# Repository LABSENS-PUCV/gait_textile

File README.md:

# gait_textile
"Detection of Human Gait Phases Using Textile Pressure Sensors: A Low Cost and Pervasive Approach" paper public repository. Created by Milovic, M.; Pizarro, F.; Fingerhuth, S.; Hermosilla, G.; Farías, G.; Yunge, D..

Based on the previous paper "Easy-to-build textile pressure sensor" published in Sensors. Created by Pizarro, F.; Villavicencio, P.; Yunge, D.; Rodríguez, M.; Hermosilla, G.; Leiva, A.

The structure of the repository is as follows:

1.- "Acquisition_board" directory contains all the files associated to the elaboration of the acquisition board used in the pants, considering PCB, code of the microcontroller, and 3D object files of the case used for the acquisition board.

2.- "Features_Classification" directory contains only one Jupyter Notebook file that contains the processes implemented to extract features from the data of the sensors, but also to elaborate the classification models and testing them.

3.- "Annotation_code" directory contains a file called "GaitAnnotation", which was written in Python and contains the method for labeling gait phases with a WebCam. This file requires a lot of libraries and BlazePose model to avhieve good 
results when assessing the position of different parts of the body.

4.- "Preprocessing" directory, which has all the Matlab code for preprocessing the data.

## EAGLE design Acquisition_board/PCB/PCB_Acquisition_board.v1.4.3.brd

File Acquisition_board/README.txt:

1.- "Case" directory contains 2 STL files that are the 3D objects printed to make the case of the acquisition board.

2.- "Code" directory contains the Arduino code loaded into an STM32 "Blue pill" development board which is part of the acquisition board.

3.- "PCB" directory includes 2 files, one of them is the layout of the PCB and the other one is the schematic diagram, both were made in Eagle.

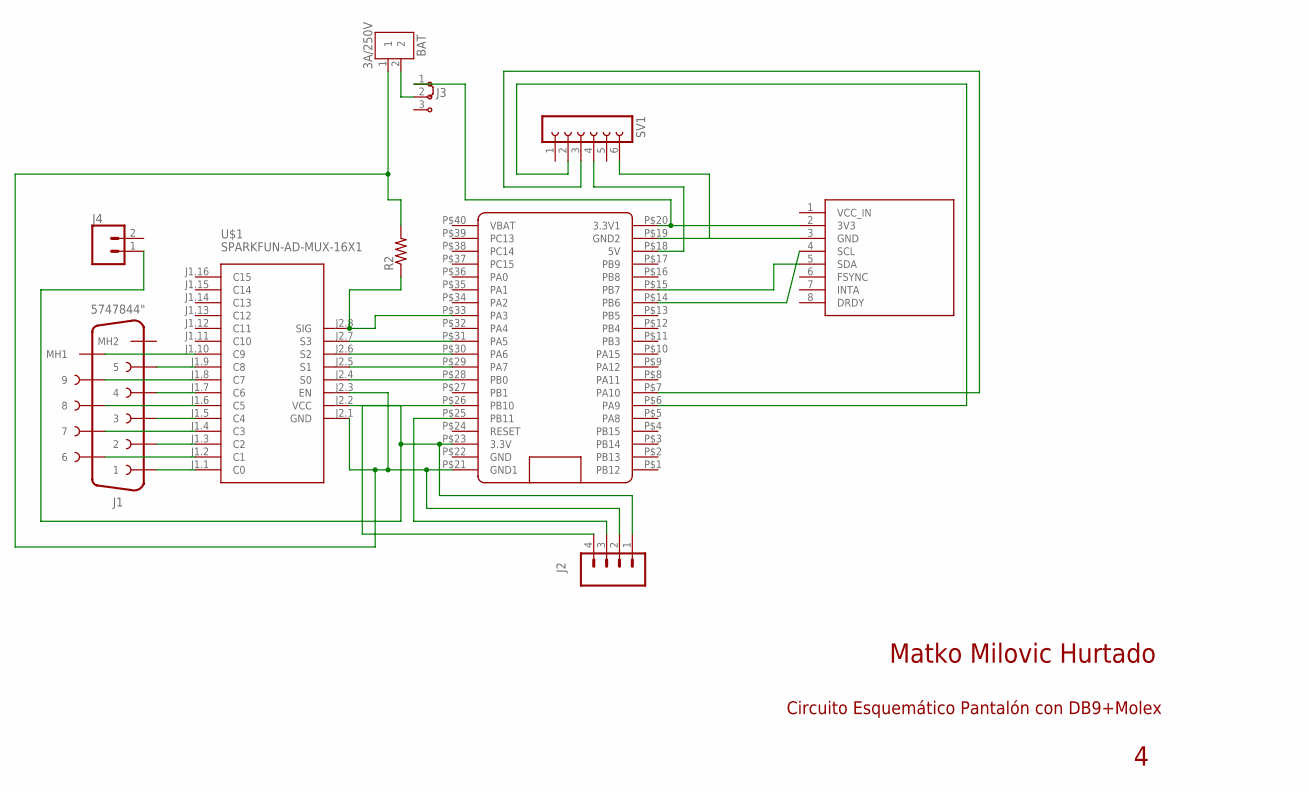
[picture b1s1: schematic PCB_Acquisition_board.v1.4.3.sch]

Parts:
BAT: 3A/250V; B2B-XH-A
J1: 5747844"; 5747844-4
J2: CONN_04; 1X04
J3: J2X2MM; 04C
J4: CONN_02; 1X02
R2: R-US_0309/10; 0309/10
SV1: FE06-1; FE06
U$1: SPARKFUN-AD-MUX-16X1
U$2: GY-86
U$5: BLUE_PILL

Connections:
MH1: J1.MH2 (MH1), U$1.J1.10 (C9)
unnamed: BAT.2, J3.2
unnamed: U$2.4 (SCL), U$5.P$14 (PB6)
unnamed: J1.1, U$1.J1.1 (C0)
unnamed: J1.6, U$1.J1.2 (C1)
unnamed: J1.2, U$1.J1.3 (C2)
unnamed: J1.7, U$1.J1.4 (C3)
unnamed: J1.3, U$1.J1.5 (C4)
unnamed: J1.8, U$1.J1.6 (C5)
unnamed: J1.4, U$1.J1.7 (C6)
unnamed: J1.9, U$1.J1.8 (C7)
unnamed: J2.3, U$5.P$25 (PB11)
unnamed: U$1.J2.4 (S0), U$5.P$28 (PB0)
unnamed: J1.5, U$1.J1.9 (C8)
unnamed: J2.1, J4.1, U$1.J2.2 (VCC), U$5.P$23 (3.3V)
unnamed: BAT.1, J2.2, R2.2, U$1.J2.1 (GND), U$1.J2.3 (EN), U$5.P$21 (GND1)
unnamed: J2.4, U$5.P$26 (PB10)
unnamed: U$2.5 (SDA), U$5.P$15 (PB7)
unnamed: SV1.3, U$5.P$7 (PA10)
unnamed: SV1.2, U$5.P$6 (PA9)
unnamed: U$1.J2.5 (S1), U$5.P$29 (PA7)
unnamed: U$1.J2.6 (S2), U$5.P$30 (PA6)
unnamed: U$1.J2.7 (S3), U$5.P$31 (PA5)
unnamed: R2.1, U$1.J2.8 (SIG), U$5.P$33 (PA3)
unnamed: SV1.6, U$2.3 (GND), U$5.P$19 (GND2)
unnamed: J3.1, U$2.2 (3V3), U$5.P$20 (3.3V1)
unnamed: SV1.4, U$5.P$18 (5V)

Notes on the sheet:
Circuito Esquemático Pantalón con DB9+Molex
Matko Milovic Hurtado

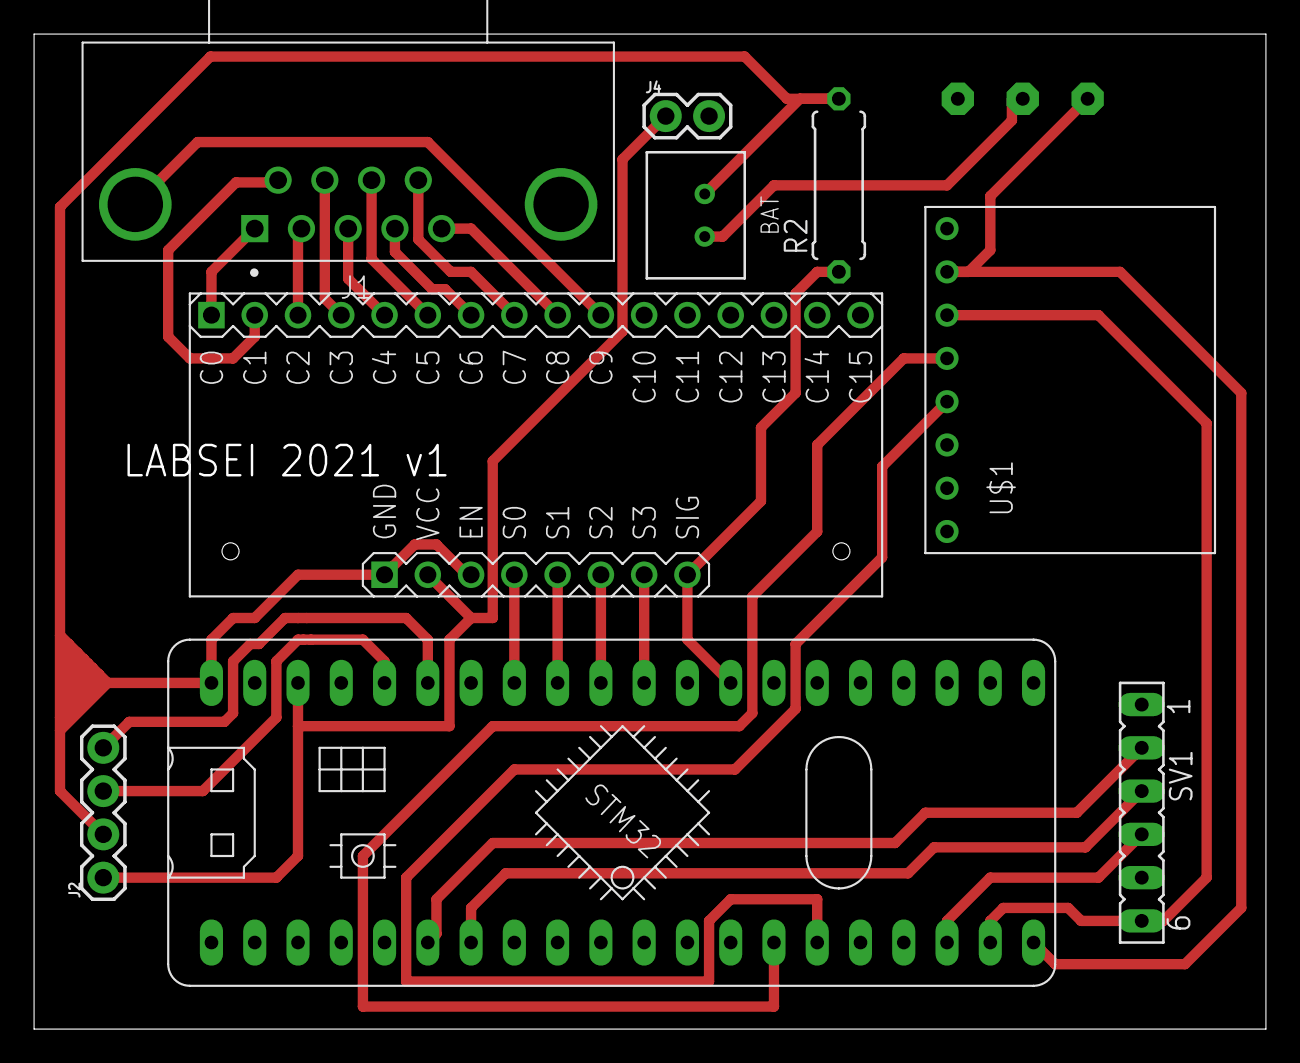
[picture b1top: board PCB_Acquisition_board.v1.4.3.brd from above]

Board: 2 copper layers, 72.3 x 58.4 mm, 10 parts (1 on the bottom side), 27 nets.

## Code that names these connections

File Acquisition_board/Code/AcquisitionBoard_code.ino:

#include "MPU9250.h"
#include <Adafruit_BMP280.h>
#include <Wire.h>

Adafruit_BMP280 bmp; // I2C
MPU9250 IMU(Wire,0x68);
int status;
float alturaB, alturaDIF;
const int num_sensores=10;
double Rref= 2200.00;                  //Resistencia del divisor de tension
unsigned long tiempus;          // Variable para almacena el tiempo de ejecucion
int S0 = PB0;
int S1 = PA7;
int S2 = PA6;
int S3 = PA5;
int muxADC = PA3;
double textiles[num_sensores] = {0.00};
double val;
double res;                        //Resistencia del sensor
double vout;                       //Voltaje del ADC
String buff = "";                  // Buffer trama

// Muestreo
volatile unsigned mactual = 0;
volatile unsigned manterior = 0;
volatile unsigned mdelta = 0;
int ts = 10;                    //tiempo de muestreo

void muestreo_mux() {
  for (int j = 0; j < num_sensores; j++){
    digitalWrite(S0, HIGH && (j & B00000001));
    digitalWrite(S1, HIGH && (j & B00000010));
    digitalWrite(S2, HIGH && (j & B00000100));
    digitalWrite(S3, HIGH && (j & B00001000));
    val = analogRead(muxADC);
    if (val<20.00){
      textiles[j]=0.00;
    }
    else{
      vout = val* 3.30;     //Formula para convertir la salida del ADC en voltaje
      vout = vout/4096;     //Formula para convertir la salida del ADC en voltaje
      textiles[j]  = Rref*((3.30/vout) -1.00);      //Calculo de la resistencia a partir del voltaje medido 
    }
  }
}

void setup() {
  
  Serial3.begin(230400);
  
  pinMode(S0, OUTPUT);
  pinMode(S1, OUTPUT);
  pinMode(S2, OUTPUT);
  pinMode(S3, OUTPUT);
  pinMode(muxADC, INPUT);
  
  if (!bmp.begin()) {
    Serial3.println(("No se encontro na el bmp"));
    while (1) delay(10);
  }

  bmp.setSampling(Adafruit_BMP280::MODE_NORMAL,     // Modo de operacion 
                  Adafruit_BMP280::SAMPLING_X2,     // Oversampling temperatura
                  Adafruit_BMP280::SAMPLING_X16,    // Oversampling presion 
                  Adafruit_BMP280::FILTER_X16,      // Filtrado.
                  Adafruit_BMP280::STANDBY_MS_63);  // Tiempo stand by. 
                  
  status = IMU.begin();
  if (status < 0) {
    Serial3.println("IMU initialization unsuccessful");
    Serial3.println("Check IMU wiring or try cycling power");
    Serial3.print("Status: ");
    Serial3.println(status);
    while(1) {}
  }
  bmp.setSampling(Adafruit_BMP280::MODE_NORMAL,     /* Operating Mode. */
                  Adafruit_BMP280::SAMPLING_X2,     /* Temp. oversampling */
                  Adafruit_BMP280::SAMPLING_X16,    /* Pressure oversampling */
                  Adafruit_BMP280::FILTER_X16,      /* Filtering. */
                  Adafruit_BMP280::STANDBY_MS_63); /* Standby time. */

  alturaB=0;
  for (int i=0;i<100;i++){
    alturaB += bmp.readAltitude(1013.25);
    delay(10);
  }
  alturaB = alturaB/100;

}

void loop() {
  mactual = millis();
  mdelta = (double) mactual - manterior;
  if (mdelta >= ts){
      IMU.readSensor();
      alturaDIF = - alturaB + bmp.readAltitude(1013.25);
      buff = buff + String(mactual, HEX)+",";
      buff = buff + String(IMU.getAccelX_mss(),2)+ "," + String(IMU.getAccelY_mss(),2)+ "," + String(IMU.getAccelZ_mss(),2)+ ",";
      buff = buff + String(IMU.getGyroX_rads(),2)+ "," + String(IMU.getGyroY_rads(),2)+ "," + String(IMU.getGyroZ_rads(),2)+ ",";
      buff = buff + String(IMU.getMagX_uT(),2)+ "," + String(IMU.getMagY_uT(),2)+ "," + String(IMU.getMagZ_uT(),2)+ ",";
      buff = buff + String(alturaDIF)+ ","; //Altitud respecto al nivel del mar en metros, averiguar bien la presion a esta altura 
      muestreo_mux();
      for(int i = 0; i < num_sensores; i ++) {
        if(i == 9) {
          buff = buff + String(int(textiles[i]))+ "!" ;
          Serial3.println(buff);
         } 
         else {
           buff = buff + String(int(textiles[i]))+ "," ;
         }
      }
      buff = "";
      manterior = mactual;
  }
}

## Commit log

2022-01-19 Segunda commit con el codigo de la tarjeta de adquisicion
2022-01-19 Todos los codigos agregados
2022-01-19 Cambio en el readme del codigo de anotacion de etiquetas
2022-02-16 Added STL files of the acquisition board
2022-02-16 Second version of it all
2022-02-16 Duplicated directory
2022-02-16 Now is in Acquisition_board folder
2022-02-16 Now is in Features_Classification folder
2022-02-16 It said "Reporte" and I translated it
2022-02-16 Removed libraries that weren't used at the end
2022-02-16 List of libraries required
2022-02-16 Brief description of the files included

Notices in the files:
parts and their libraries:
SparkFun-Connectors: Licensing: Creative Commons ShareAlike 4.0 International - https://creativecommons.org/licenses/by-sa/4.0
diy-modules: Released under the Creative Commons Attribution 4.0 International License: http://creativecommons.org/licenses/by/4.0
